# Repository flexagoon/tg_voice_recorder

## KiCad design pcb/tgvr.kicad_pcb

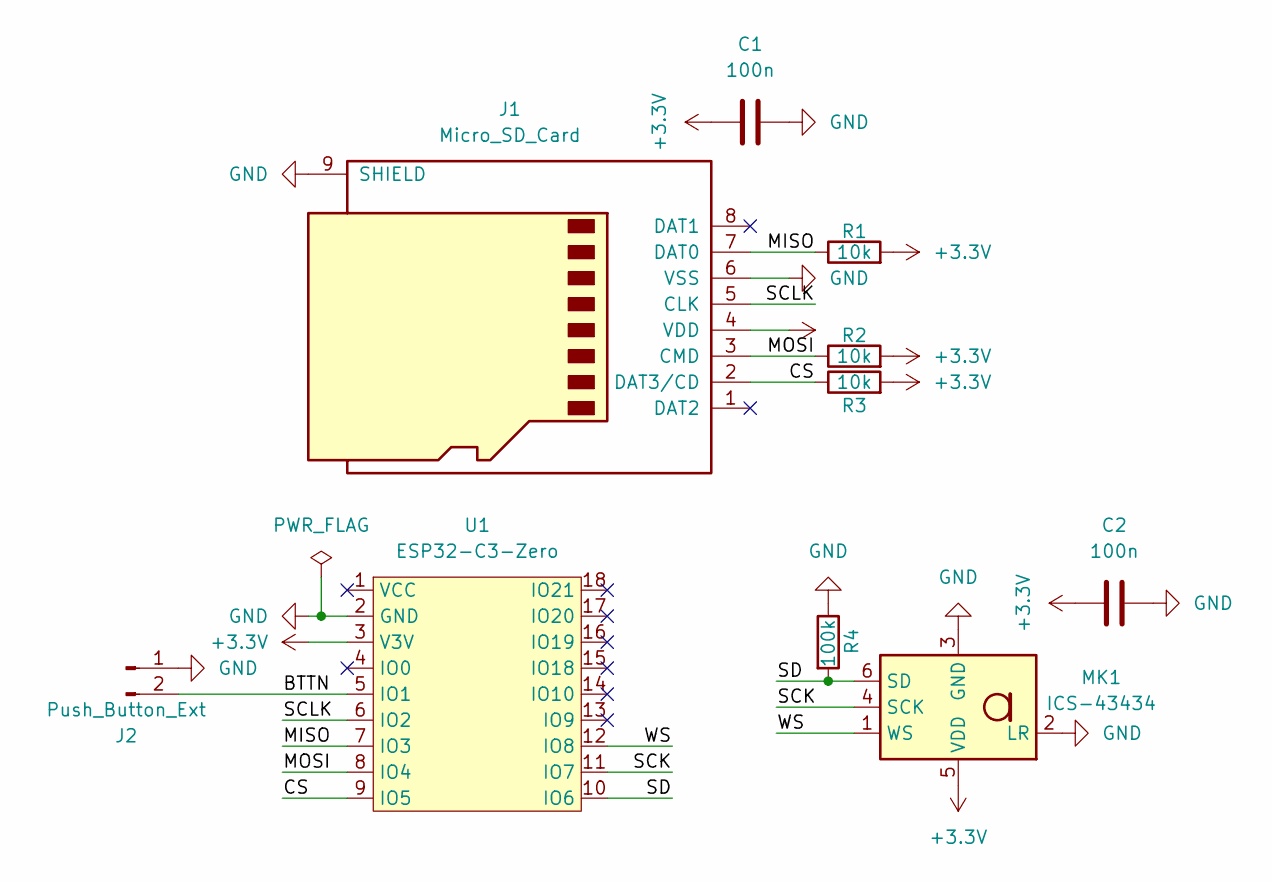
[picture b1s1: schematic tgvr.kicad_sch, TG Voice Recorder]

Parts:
C1, C2: 100n; C_0603_1608Metric_Pad1.08x0.95mm_HandSolder
J1: Micro_SD_Card; microSD_HC_Molex_47219-2001
J2: Push_Button_Ext; SolderWire-0.5sqmm_1x02_P4.8mm_D0.9mm_OD2.3mm
MK1: ICS-43434; InvenSense_ICS-43434-6_3.5x2.65mm
R1, R2, R3: 10k; R_0805_2012Metric_Pad1.20x1.40mm_HandSolder
R4: 100k; R_0805_2012Metric_Pad1.20x1.40mm_HandSolder
U1: ESP32-C3-Zero; Waveshare-ESP32-C3-Zero

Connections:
+3.3V: C1.1, C2.1, J1.4 (VDD), MK1.5 (VDD), R1.2, R2.2, R3.2, U1.3 (V3V)
/BTTN: J2.2, U1.5 (IO1)
/CS: J1.2 (DAT3/CD), R3.1, U1.9 (IO5)
/MISO: J1.7 (DAT0), R1.1, U1.7 (IO3)
/MOSI: J1.3 (CMD), R2.1, U1.8 (IO4)
/SCK: MK1.4 (SCK), U1.11 (IO7)
/SCLK: J1.5 (CLK), U1.6 (IO2)
/SD: MK1.6 (SD), R4.2, U1.10 (IO6)
/WS: MK1.1 (WS), U1.12 (IO8)
GND: C1.2, C2.2, J1.6 (VSS), J1.9 (SHIELD), J2.1, MK1.2 (LR), MK1.3 (GND), R4.1, U1.2 (GND)

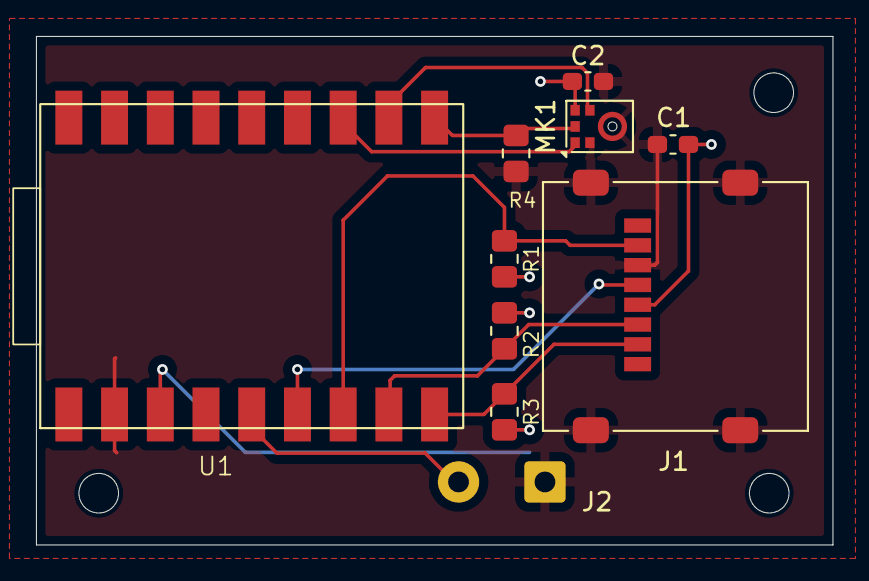
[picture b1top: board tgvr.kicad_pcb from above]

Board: 2 copper layers, 44.3 x 28.2 mm, 10 parts (0 on the bottom side), 10 nets.

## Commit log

2025-06-16 feat: implement the wifi component
2025-06-16 refactor: move wifi.h directly into the component directory
2025-06-16 feat: implement the sd component
2025-06-18 feat(wifi): improve connection attempt handling
2025-06-18 feat(wifi): initialize NVS before wifi
2025-06-18 feat(sd): add logging
2025-06-18 feat(telegram): implement the telegram component
2025-06-18 build: enable minimal build
2025-06-18 feat(sd): add error handling
2025-06-18 feat(wifi): add error handling
2025-06-18 feat(telegram): add error handling
2025-06-18 fix(telegram): reduce the connection timeout
2025-06-18 refactor: use check macros for file error handling
2025-08-27 fix: use proper import in main for check macros
2025-12-06 feat(microphone): add i2s microphone initialization
2025-12-06 refactor: add const where possible
2025-12-06 feat(microphone): implement audio recording
2025-12-07 feat(button): create the button handler
2025-12-07 feat(microphone): attach recording to a button-triggered task
2026-01-07 feat(pcb): create the pcb design
2026-01-25 feat(microphone): name audio files with current time
2026-01-25 feat(wifi): initialize SNTP
2026-01-25 feat(microphone): make the bitshift configurable
2026-01-25 feat(microphone,telegram): send voice recordings to telegram
